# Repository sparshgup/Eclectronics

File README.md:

# Eclectronics
Olin College - Spring 2025 - Eclectronics

## [RP2350A Development Board](https://github.com/sparshgup/Eclectronics/tree/main/RP2350Adev)

## [MP1: USB-powered LED Flasher](https://github.com/sparshgup/Eclectronics/tree/main/MP1)

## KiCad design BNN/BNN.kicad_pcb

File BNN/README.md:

# Binary Neural Network Inference Accelerator PCB

Built a custom 2-layer PCB that combines an RP2040 microcontroller with a Lattice iCE40UP5K FPGA. The goal was to run a small binary neural network (BNN) classifier on the FPGA in hardware. The RP2040 programs the FPGA, sends input data over SPI, gets back a classification result, and prints it over USB serial. An RGB LED shows which class was picked.

BNNs use XNOR and popcount instead of floating-point math, which maps well onto FPGA lookup tables. The demo targets the Iris dataset (4 inputs, 3 classes). The hardware doesn't care what model you use since the weights are just baked into the FPGA bitstream.

The design is based on the open-source pico-ice board by tinyVision.ai and the riffpga framework by Psychogenic Technologies.

## Layout

## PCB

## Schematics

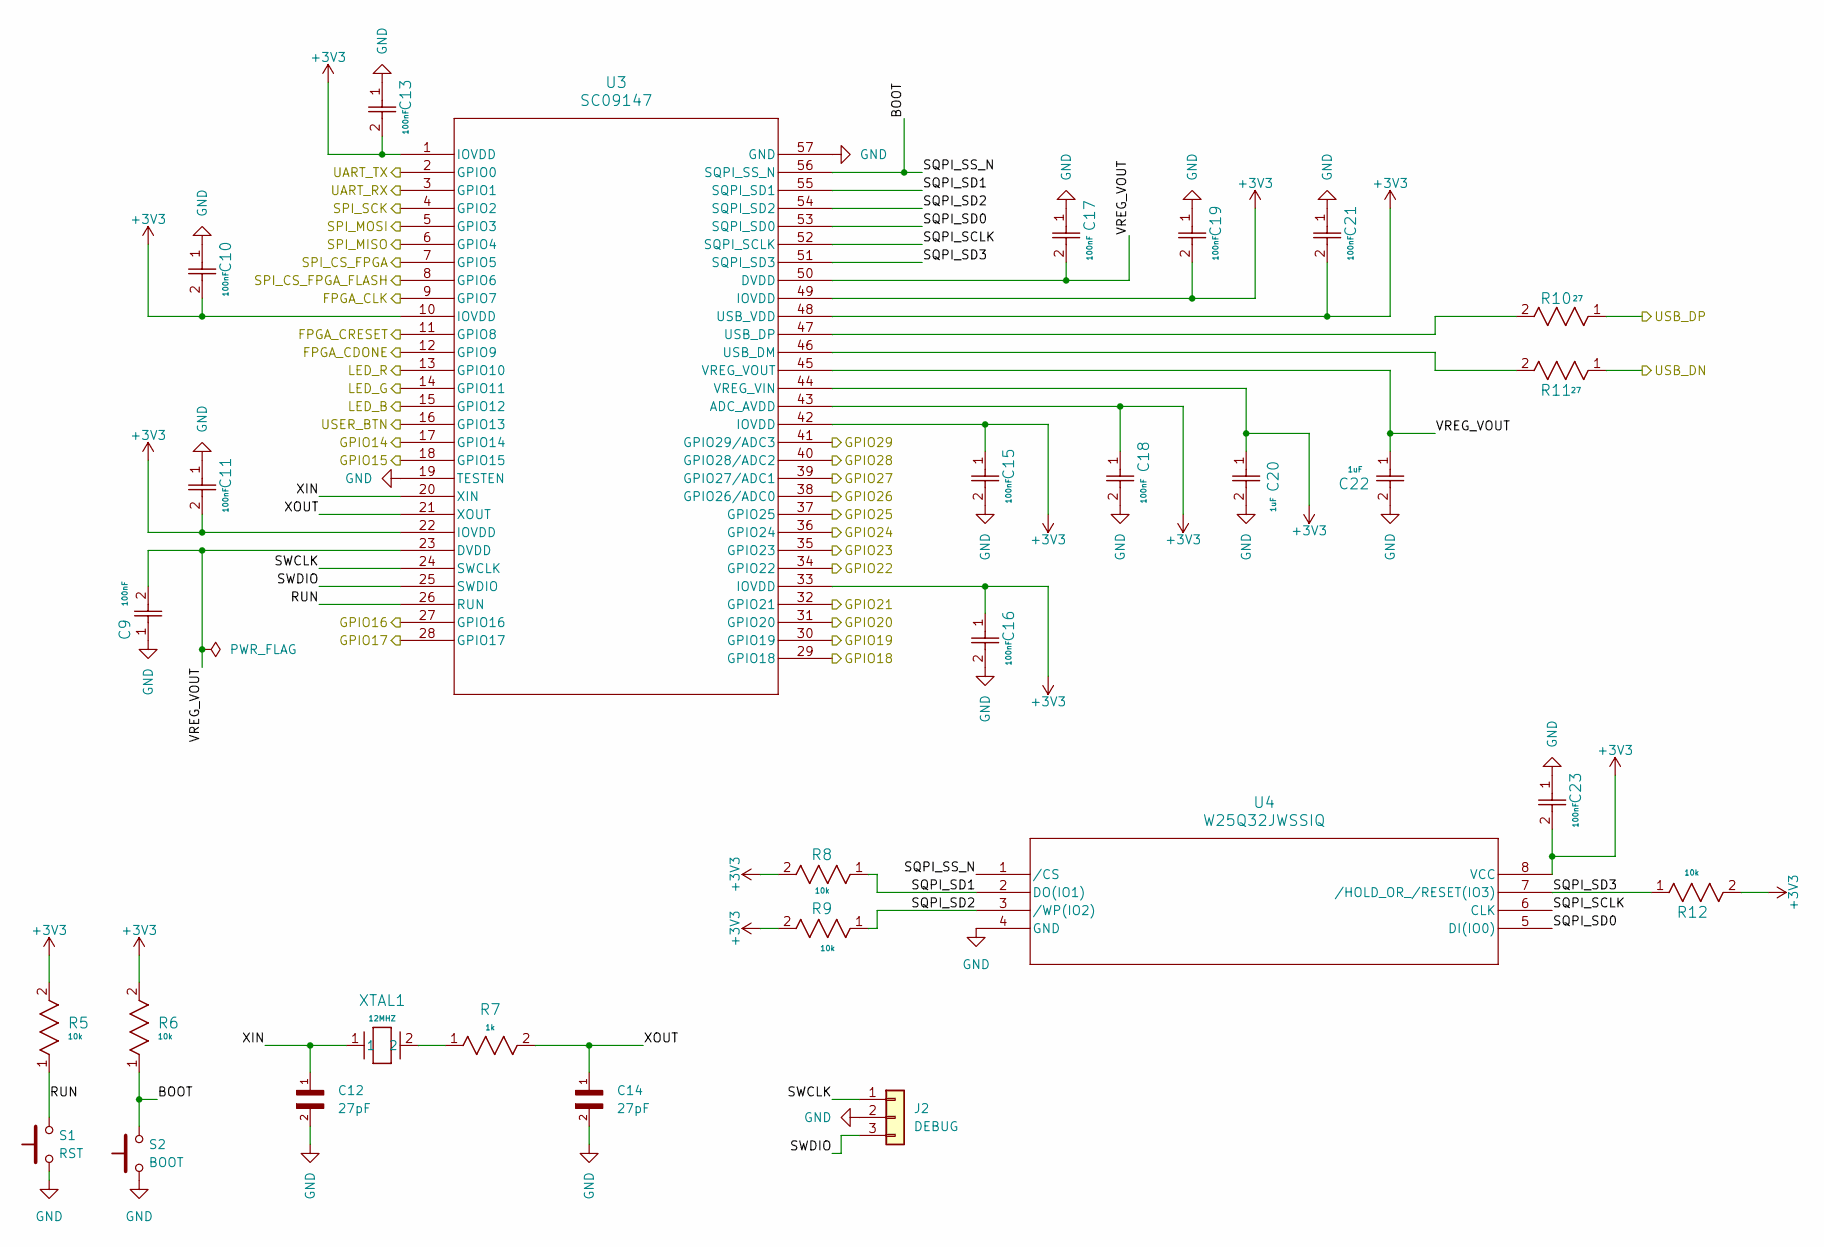
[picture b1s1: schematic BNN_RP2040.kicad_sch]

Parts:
C9, C10, C11, C13, C15, C16, C17, C18, C19, C21, C23: 100nF; CAP_CL10_SAM
C12, C14: 27pF; CAPC1608X90N; DigiKey_Part_Number 490-17767-1-ND
C20, C22: 1uF; CAP_GCM188_MUR
J2: DEBUG; PinHeader_1x03_P2.54mm_Vertical
R5, R6, R8, R9, R12: 10k; RC0603N_PAN
R7: 1k; RC0603N_YAG
R10, R11: 27; RC0603N_YAG
S1: RST; B3U-1000P
S2: BOOT; B3U-1000P
U3: SC09147; QFN56_7X7_RPI
U4: W25Q32JWSSIQ; SOIC-8_5P28X5P28_WIN
XTAL1: 12MHZ; XTAL_ABLS_ABR

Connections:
+3V3: C10.2, C11.2, C13.2, C15.1, C16.1, C18.1, C19.2, C20.1, C21.2, C23.2, R5.2, R6.2, R8.2, R9.2, R12.2, U3.1 (IOVDD), U3.10 (IOVDD), U3.22 (IOVDD), U3.33 (IOVDD), U3.42 (IOVDD), U3.43 (ADC_AVDD), U3.44 (VREG_VIN), U3.48 (USB_VDD), U3.49 (IOVDD), U4.8 (VCC); also elsewhere on the board
/IO/GPIO14: U3.17 (GPIO14); also elsewhere on the board
/IO/GPIO15: U3.18 (GPIO15); also elsewhere on the board
/IO/GPIO16: U3.27 (GPIO16); also elsewhere on the board
/IO/GPIO17: U3.28 (GPIO17); also elsewhere on the board
/IO/GPIO18: U3.29 (GPIO18); also elsewhere on the board
/IO/GPIO19: U3.30 (GPIO19); also elsewhere on the board
/IO/GPIO20: U3.31 (GPIO20); also elsewhere on the board
/IO/GPIO21: U3.32 (GPIO21); also elsewhere on the board
/IO/GPIO22: U3.34 (GPIO22); also elsewhere on the board
/IO/GPIO23: U3.35 (GPIO23); also elsewhere on the board
/IO/GPIO24: U3.36 (GPIO24); also elsewhere on the board
/IO/GPIO25: U3.37 (GPIO25); also elsewhere on the board
/IO/GPIO26: U3.38 (GPIO26/ADC0); also elsewhere on the board
/IO/GPIO27: U3.39 (GPIO27/ADC1); also elsewhere on the board
/IO/GPIO28: U3.40 (GPIO28/ADC2); also elsewhere on the board
/IO/GPIO29: U3.41 (GPIO29/ADC3); also elsewhere on the board
/IO/LED_B: U3.15 (GPIO12); also elsewhere on the board
/IO/LED_G: U3.14 (GPIO11); also elsewhere on the board
/IO/LED_R: U3.13 (GPIO10); also elsewhere on the board
/IO/USER_BTN: U3.16 (GPIO13); also elsewhere on the board
/Power/USB_DN: R11.1; also elsewhere on the board
/Power/USB_DP: R10.1; also elsewhere on the board
/RP2040/BOOT: R6.1, S2.2, U3.56 (SQPI_SS_N), U4.1 (/CS)
/RP2040/FPGA_CDONE: U3.12 (GPIO9); also elsewhere on the board
/RP2040/FPGA_CLK: U3.9 (GPIO7); also elsewhere on the board
/RP2040/FPGA_CRESET: U3.11 (GPIO8); also elsewhere on the board
/RP2040/RUN: R5.1, S1.2, U3.26 (RUN)
/RP2040/SPI_CS_FPGA: U3.7 (GPIO5); also elsewhere on the board
/RP2040/SQPI_SCLK: U3.52 (SQPI_SCLK), U4.6 (CLK)
/RP2040/SQPI_SD0: U3.53 (SQPI_SD0), U4.5 (DI(IO0))
/RP2040/SQPI_SD1: R8.1, U3.55 (SQPI_SD1), U4.2 (DO(IO1))
/RP2040/SQPI_SD2: R9.1, U3.54 (SQPI_SD2), U4.3 (/WP(IO2))
/RP2040/SQPI_SD3: R12.1, U3.51 (SQPI_SD3), U4.7 (/HOLD_OR_/RESET(IO3))
/RP2040/SWCLK: J2.1, U3.24 (SWCLK)
/RP2040/SWDIO: J2.3, U3.25 (SWDIO)
/RP2040/UART_RX: U3.3 (GPIO1); also elsewhere on the board
/RP2040/UART_TX: U3.2 (GPIO0); also elsewhere on the board
/RP2040/VREG_VOUT: C9.2, C17.2, C22.1, U3.23 (DVDD), U3.45 (VREG_VOUT), U3.50 (DVDD)
/RP2040/XIN: C12.1, U3.20 (XIN), XTAL1.1
/RP2040/XOUT: C14.1, R7.2, U3.21 (XOUT)
/iCE40UP5K/SPI_S0: U3.6 (GPIO4); also elsewhere on the board
/iCE40UP5K/SPI_SCK: U3.4 (GPIO2); also elsewhere on the board
/iCE40UP5K/SPI_SI: U3.5 (GPIO3); also elsewhere on the board
/iCE40UP5K/SPI_SS: U3.8 (GPIO6); also elsewhere on the board
GND: C9.1, C10.1, C11.1, C12.2, C13.1, C14.2, C15.2, C16.2, C17.1, C18.2, C19.1, C20.2, C21.1, C22.2, C23.1, J2.2, S1.1, S2.1, U3.19 (TESTEN), U3.57 (GND), U4.4 (GND); also elsewhere on the board
unnamed: R7.1, XTAL1.2
unnamed: R11.2, U3.46 (USB_DM)
unnamed: R10.2, U3.47 (USB_DP)

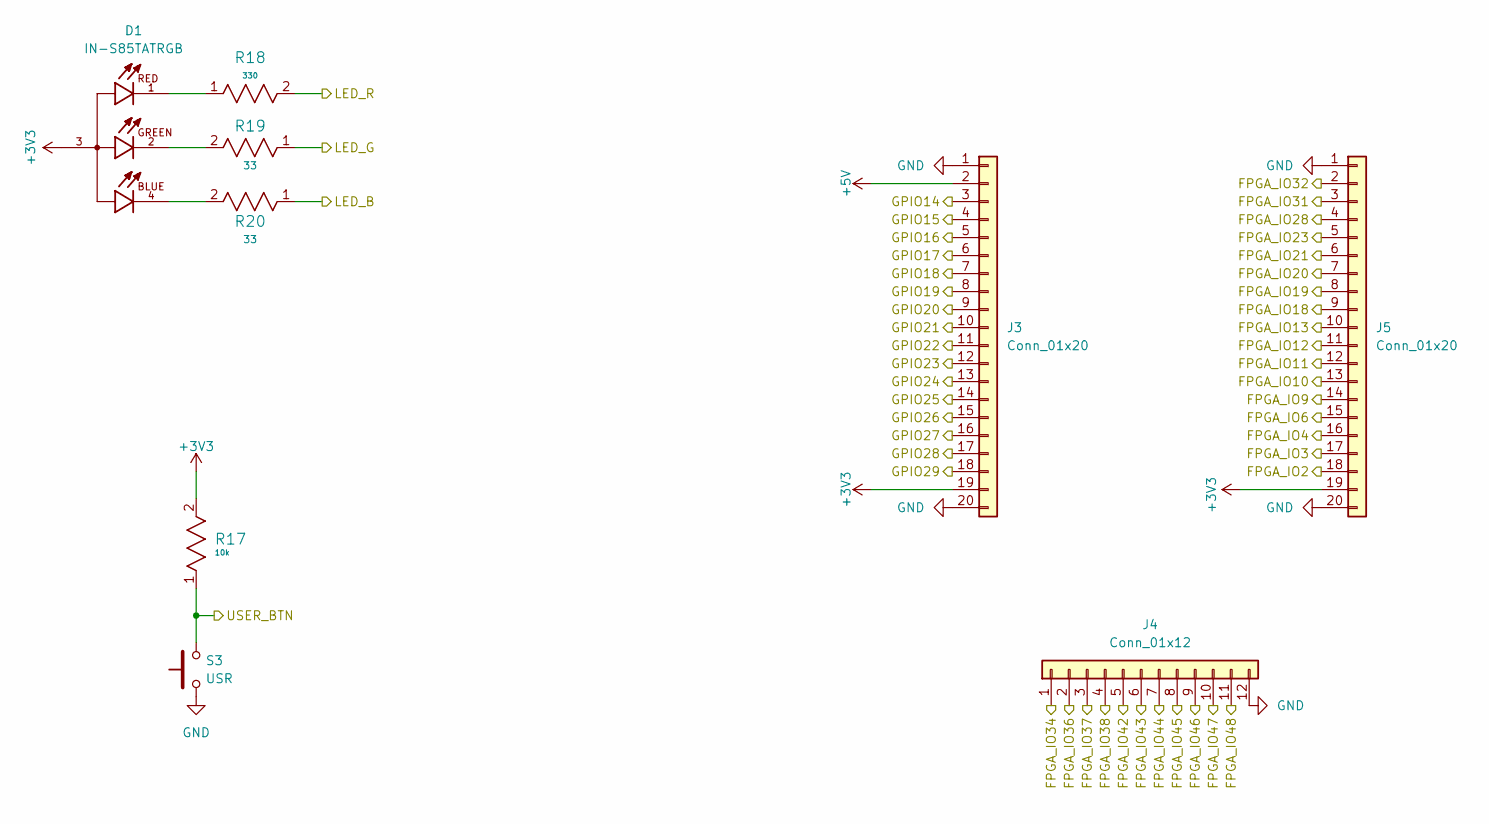
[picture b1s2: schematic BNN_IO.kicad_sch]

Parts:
D1: IN-S85TATRGB; LEDSC70P200X125X110-4N; PARTREV 1.0; DigiKey_Part_Number 1830-1086-1-ND
J3, J5: Conn_01x20; PinHeader_1x20_P2.54mm_Vertical
J4: Conn_01x12; PinHeader_1x12_P2.54mm_Vertical
R17: 10k; RC0603N_PAN
R18: 330; RC0603N_YAG
R19, R20: 33; RC0603N_YAG
S3: USR; B3U-1000P

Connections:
+3V3: D1.3, J3.19, J5.19, R17.2; also elsewhere on the board
+5V: J3.2; also elsewhere on the board
/IO/FPGA_IO2: J5.18; also elsewhere on the board
/IO/FPGA_IO3: J5.17; also elsewhere on the board
/IO/FPGA_IO4: J5.16; also elsewhere on the board
/IO/FPGA_IO6: J5.15; also elsewhere on the board
/IO/FPGA_IO9: J5.14; also elsewhere on the board
/IO/FPGA_IO10: J5.13; also elsewhere on the board
/IO/FPGA_IO11: J5.12; also elsewhere on the board
/IO/FPGA_IO12: J5.11; also elsewhere on the board
/IO/FPGA_IO13: J5.10; also elsewhere on the board
/IO/FPGA_IO18: J5.9; also elsewhere on the board
/IO/FPGA_IO19: J5.8; also elsewhere on the board
/IO/FPGA_IO20: J5.7; also elsewhere on the board
/IO/FPGA_IO21: J5.6; also elsewhere on the board
/IO/FPGA_IO23: J5.5; also elsewhere on the board
/IO/FPGA_IO28: J5.4; also elsewhere on the board
/IO/FPGA_IO31: J5.3; also elsewhere on the board
/IO/FPGA_IO32: J5.2; also elsewhere on the board
/IO/FPGA_IO34: J4.1; also elsewhere on the board
/IO/FPGA_IO36: J4.2; also elsewhere on the board
/IO/FPGA_IO37: J4.3; also elsewhere on the board
/IO/FPGA_IO38: J4.4; also elsewhere on the board
/IO/FPGA_IO42: J4.5; also elsewhere on the board
/IO/FPGA_IO43: J4.6; also elsewhere on the board
/IO/FPGA_IO44: J4.7; also elsewhere on the board
/IO/FPGA_IO45: J4.8; also elsewhere on the board
/IO/FPGA_IO46: J4.9; also elsewhere on the board
/IO/FPGA_IO47: J4.10; also elsewhere on the board
/IO/FPGA_IO48: J4.11; also elsewhere on the board
/IO/GPIO14: J3.3; also elsewhere on the board
/IO/GPIO15: J3.4; also elsewhere on the board
/IO/GPIO16: J3.5; also elsewhere on the board
/IO/GPIO17: J3.6; also elsewhere on the board
/IO/GPIO18: J3.7; also elsewhere on the board
/IO/GPIO19: J3.8; also elsewhere on the board
/IO/GPIO20: J3.9; also elsewhere on the board
/IO/GPIO21: J3.10; also elsewhere on the board
/IO/GPIO22: J3.11; also elsewhere on the board
/IO/GPIO23: J3.12; also elsewhere on the board
/IO/GPIO24: J3.13; also elsewhere on the board
/IO/GPIO25: J3.14; also elsewhere on the board
/IO/GPIO26: J3.15; also elsewhere on the board
/IO/GPIO27: J3.16; also elsewhere on the board
/IO/GPIO28: J3.17; also elsewhere on the board
/IO/GPIO29: J3.18; also elsewhere on the board
/IO/LED_B: R20.1; also elsewhere on the board
/IO/LED_G: R19.1; also elsewhere on the board
/IO/LED_R: R18.2; also elsewhere on the board
/IO/USER_BTN: R17.1, S3.2; also elsewhere on the board
GND: J3.1, J3.20, J4.12, J5.1, J5.20, S3.1; also elsewhere on the board
unnamed: D1.1, R18.1
unnamed: D1.2, R19.2
unnamed: D1.4, R20.2

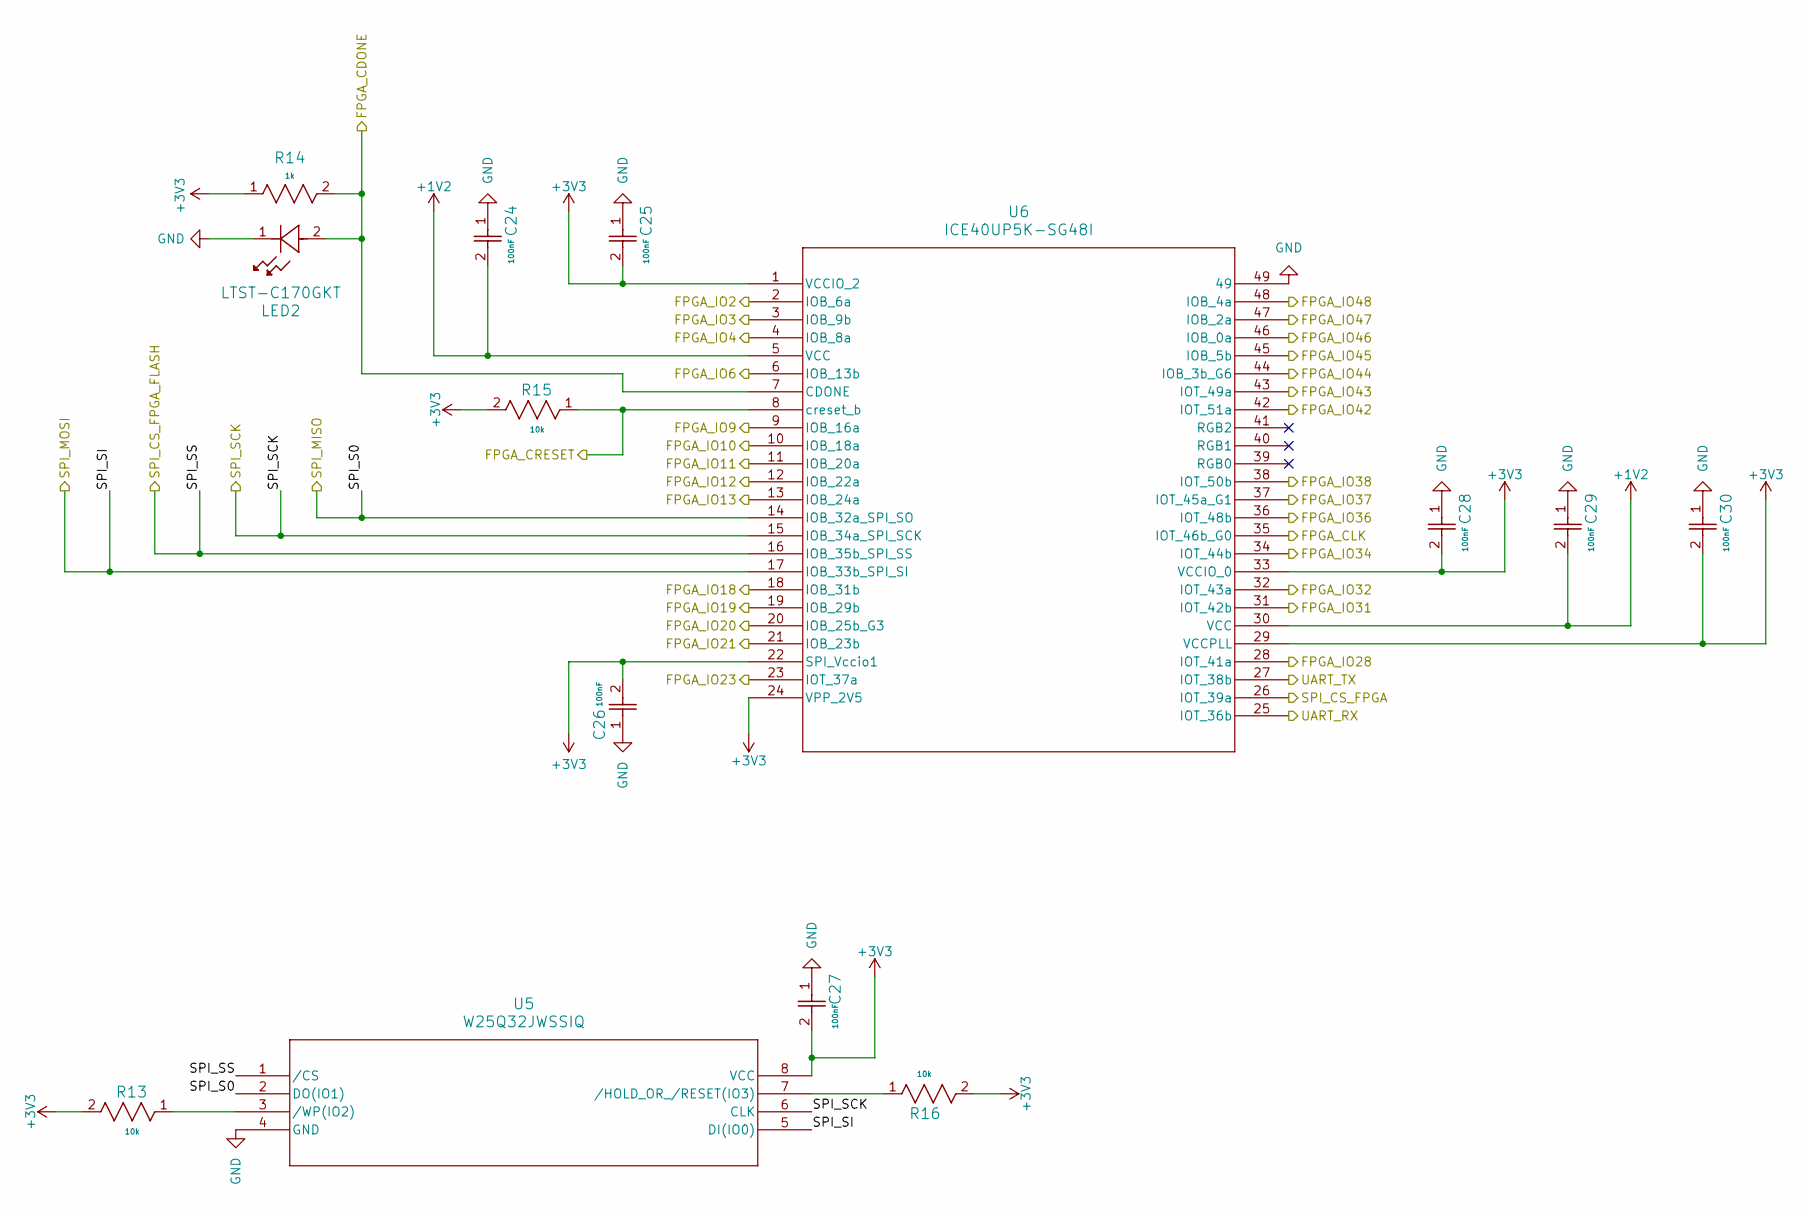
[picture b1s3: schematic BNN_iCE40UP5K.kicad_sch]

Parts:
C24, C25, C26, C27, C28, C29, C30: 100nF; CAP_CL10_SAM
LED2: LTST-C170GKT; LED_LTST-C170GKT_LTO
R13, R15, R16: 10k; RC0603N_PAN
R14: 1k; RC0603N_YAG
U5: W25Q32JWSSIQ; SOIC-8_5P28X5P28_WIN
U6: ICE40UP5K-SG48I; QFN-48-1EP_7x7mm_P0.5mm_EP5.6x5.6mm

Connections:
+1V2: C24.2, C29.2, U6.5 (VCC), U6.30 (VCC); also elsewhere on the board
+3V3: C25.2, C26.2, C27.2, C28.2, C30.2, R13.2, R14.1, R15.2, R16.2, U5.8 (VCC), U6.1 (VCCIO_2), U6.22 (SPI_Vccio1), U6.24 (VPP_2V5), U6.29 (VCCPLL), U6.33 (VCCIO_0); also elsewhere on the board
/IO/FPGA_IO2: U6.2 (IOB_6a); also elsewhere on the board
/IO/FPGA_IO3: U6.3 (IOB_9b); also elsewhere on the board
/IO/FPGA_IO4: U6.4 (IOB_8a); also elsewhere on the board
/IO/FPGA_IO6: U6.6 (IOB_13b); also elsewhere on the board
/IO/FPGA_IO9: U6.9 (IOB_16a); also elsewhere on the board
/IO/FPGA_IO10: U6.10 (IOB_18a); also elsewhere on the board
/IO/FPGA_IO11: U6.11 (IOB_20a); also elsewhere on the board
/IO/FPGA_IO12: U6.12 (IOB_22a); also elsewhere on the board
/IO/FPGA_IO13: U6.13 (IOB_24a); also elsewhere on the board
/IO/FPGA_IO18: U6.18 (IOB_31b); also elsewhere on the board
/IO/FPGA_IO19: U6.19 (IOB_29b); also elsewhere on the board
/IO/FPGA_IO20: U6.20 (IOB_25b_G3); also elsewhere on the board
/IO/FPGA_IO21: U6.21 (IOB_23b); also elsewhere on the board
/IO/FPGA_IO23: U6.23 (IOT_37a); also elsewhere on the board
/IO/FPGA_IO28: U6.28 (IOT_41a); also elsewhere on the board
/IO/FPGA_IO31: U6.31 (IOT_42b); also elsewhere on the board
/IO/FPGA_IO32: U6.32 (IOT_43a); also elsewhere on the board
/IO/FPGA_IO34: U6.34 (IOT_44b); also elsewhere on the board
/IO/FPGA_IO36: U6.36 (IOT_48b); also elsewhere on the board
/IO/FPGA_IO37: U6.37 (IOT_45a_G1); also elsewhere on the board
/IO/FPGA_IO38: U6.38 (IOT_50b); also elsewhere on the board
/IO/FPGA_IO42: U6.42 (IOT_51a); also elsewhere on the board
/IO/FPGA_IO43: U6.43 (IOT_49a); also elsewhere on the board
/IO/FPGA_IO44: U6.44 (IOB_3b_G6); also elsewhere on the board
/IO/FPGA_IO45: U6.45 (IOB_5b); also elsewhere on the board
/IO/FPGA_IO46: U6.46 (IOB_0a); also elsewhere on the board
/IO/FPGA_IO47: U6.47 (IOB_2a); also elsewhere on the board
/IO/FPGA_IO48: U6.48 (IOB_4a); also elsewhere on the board
/RP2040/FPGA_CDONE: LED2.2, R14.2, U6.7 (CDONE); also elsewhere on the board
/RP2040/FPGA_CLK: U6.35 (IOT_46b_G0); also elsewhere on the board
/RP2040/FPGA_CRESET: R15.1, U6.8 (creset_b); also elsewhere on the board
/RP2040/SPI_CS_FPGA: U6.26 (IOT_39a); also elsewhere on the board
/RP2040/UART_RX: U6.25 (IOT_36b); also elsewhere on the board
/RP2040/UART_TX: U6.27 (IOT_38b); also elsewhere on the board
/iCE40UP5K/SPI_S0: U5.2 (DO(IO1)), U6.14 (IOB_32a_SPI_SO); also elsewhere on the board
/iCE40UP5K/SPI_SCK: U5.6 (CLK), U6.15 (IOB_34a_SPI_SCK); also elsewhere on the board
/iCE40UP5K/SPI_SI: U5.5 (DI(IO0)), U6.17 (IOB_33b_SPI_SI); also elsewhere on the board
/iCE40UP5K/SPI_SS: U5.1 (/CS), U6.16 (IOB_35b_SPI_SS); also elsewhere on the board
GND: C24.1, C25.1, C26.1, C27.1, C28.1, C29.1, C30.1, LED2.1, U5.4 (GND), U6.49; also elsewhere on the board
unnamed: R16.1, U5.7 (/HOLD_OR_/RESET(IO3))
unnamed: R13.1, U5.3 (/WP(IO2))

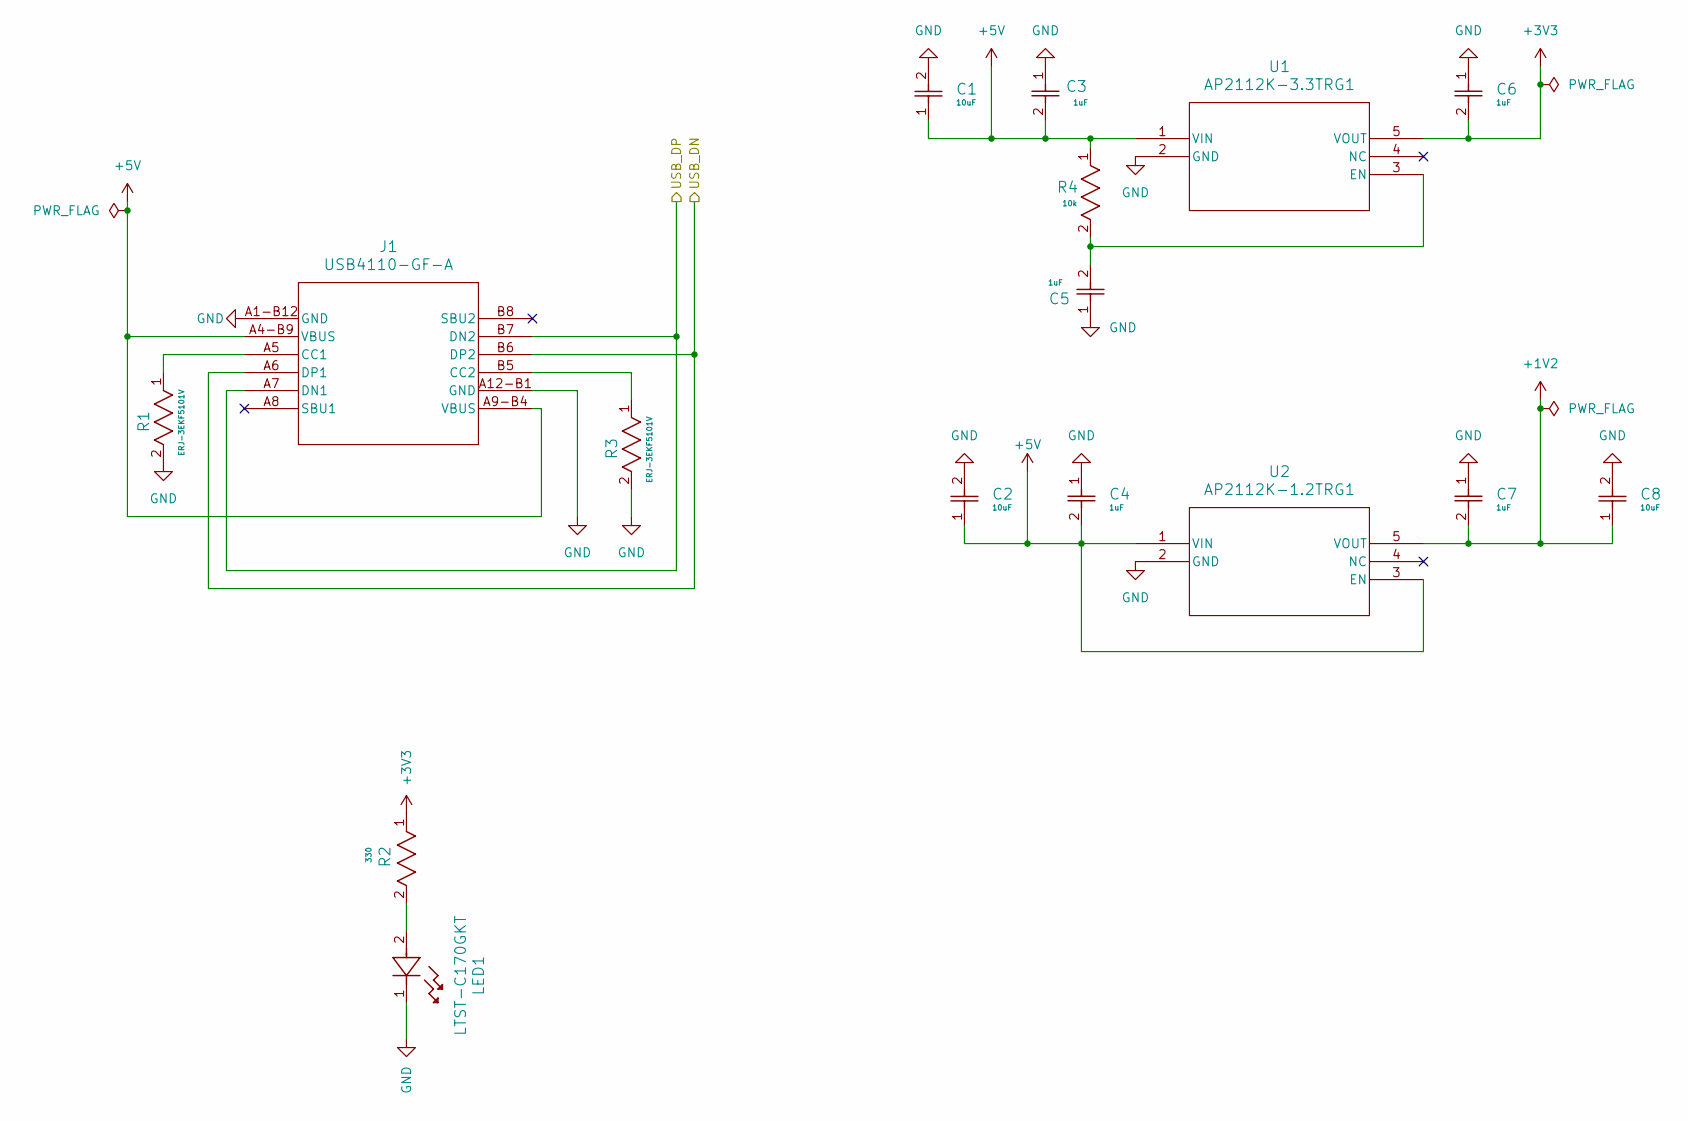
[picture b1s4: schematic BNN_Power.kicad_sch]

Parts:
C1, C2, C8: 10uF; CAP_GRM188_&plus_&slash_-0.2_MUR
C3, C4, C5, C6, C7: 1uF; CAP_GCM188_MUR
J1: USB4110-GF-A; USB4110-GF-A_GCT
LED1: LTST-C170GKT; LED_LTST-C170GKT_LTO
R1, R3: ERJ-3EKF5101V; RC0603N_PAN
R2: 330; RC0603N_YAG
R4: 10k; RC0603N_PAN
U1: AP2112K-3.3TRG1; SOT_RG1_DIO
U2: AP2112K-1.2TRG1; SOT_RG1_DIO

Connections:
+1V2: C7.2, C8.1, U2.5 (VOUT); also elsewhere on the board
+3V3: C6.2, R2.1, U1.5 (VOUT); also elsewhere on the board
+5V: C1.1, C2.1, C3.2, C4.2, J1.A4-B9 (VBUS), J1.A9-B4 (VBUS), R4.1, U1.1 (VIN), U2.1 (VIN), U2.3 (EN); also elsewhere on the board
/Power/USB_DN: J1.A6 (DP1), J1.B6 (DP2); also elsewhere on the board
/Power/USB_DP: J1.A7 (DN1), J1.B7 (DN2); also elsewhere on the board
GND: C1.2, C2.2, C3.1, C4.1, C5.1, C6.1, C7.1, C8.2, J1.A1-B12 (GND), J1.A12-B1 (GND), LED1.1, R1.2, R3.2, U1.2 (GND), U2.2 (GND); also elsewhere on the board
unnamed: J1.A5 (CC1), R1.1
unnamed: J1.B5 (CC2), R3.1
unnamed: LED1.2, R2.2
unnamed: C5.2, R4.2, U1.3 (EN)

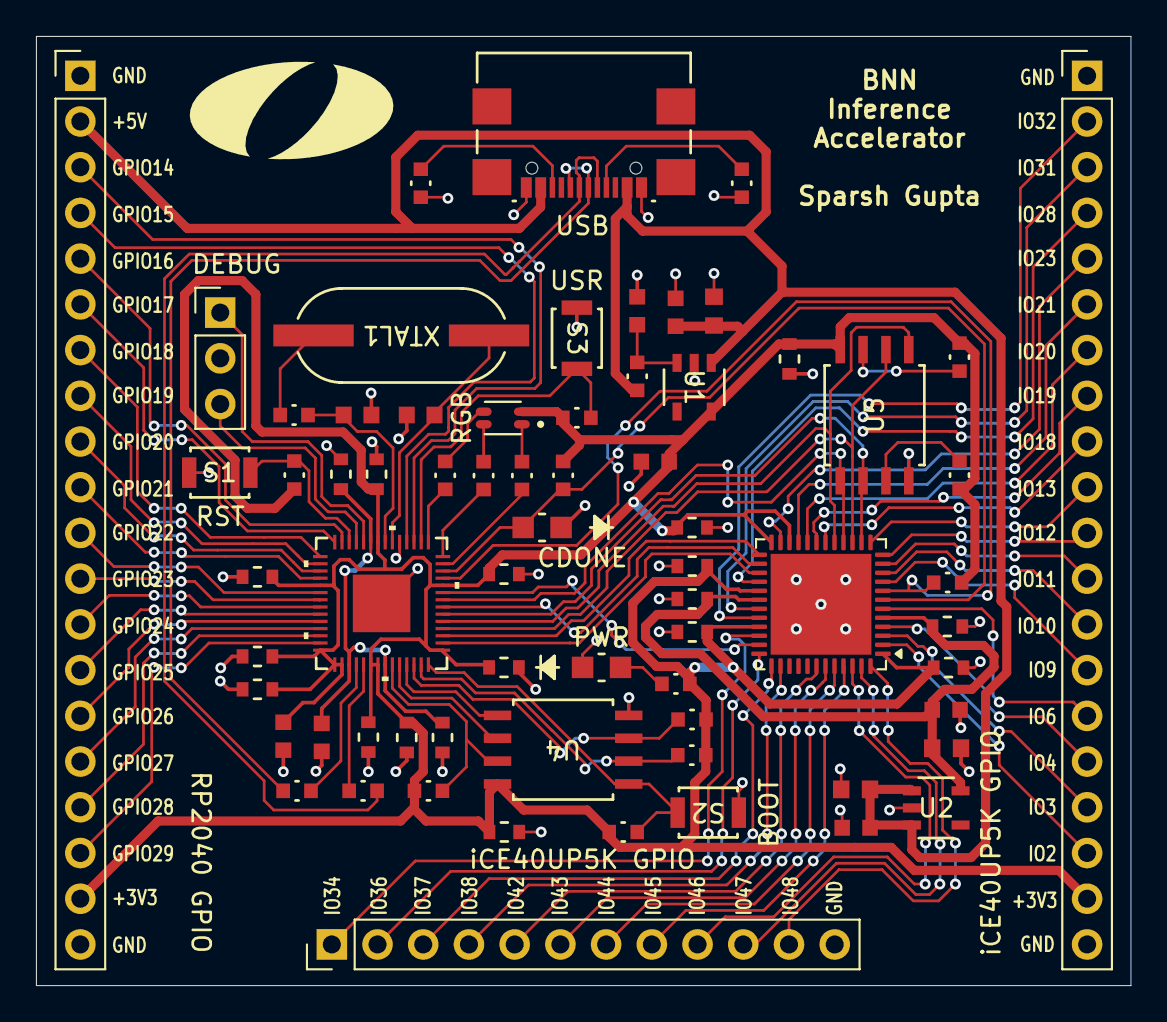
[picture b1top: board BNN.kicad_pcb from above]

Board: 2 copper layers, 60.8 x 52.7 mm, 69 parts (0 on the bottom side), 88 nets.

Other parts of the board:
OlinLogoLg: G***; OlinLogoLg

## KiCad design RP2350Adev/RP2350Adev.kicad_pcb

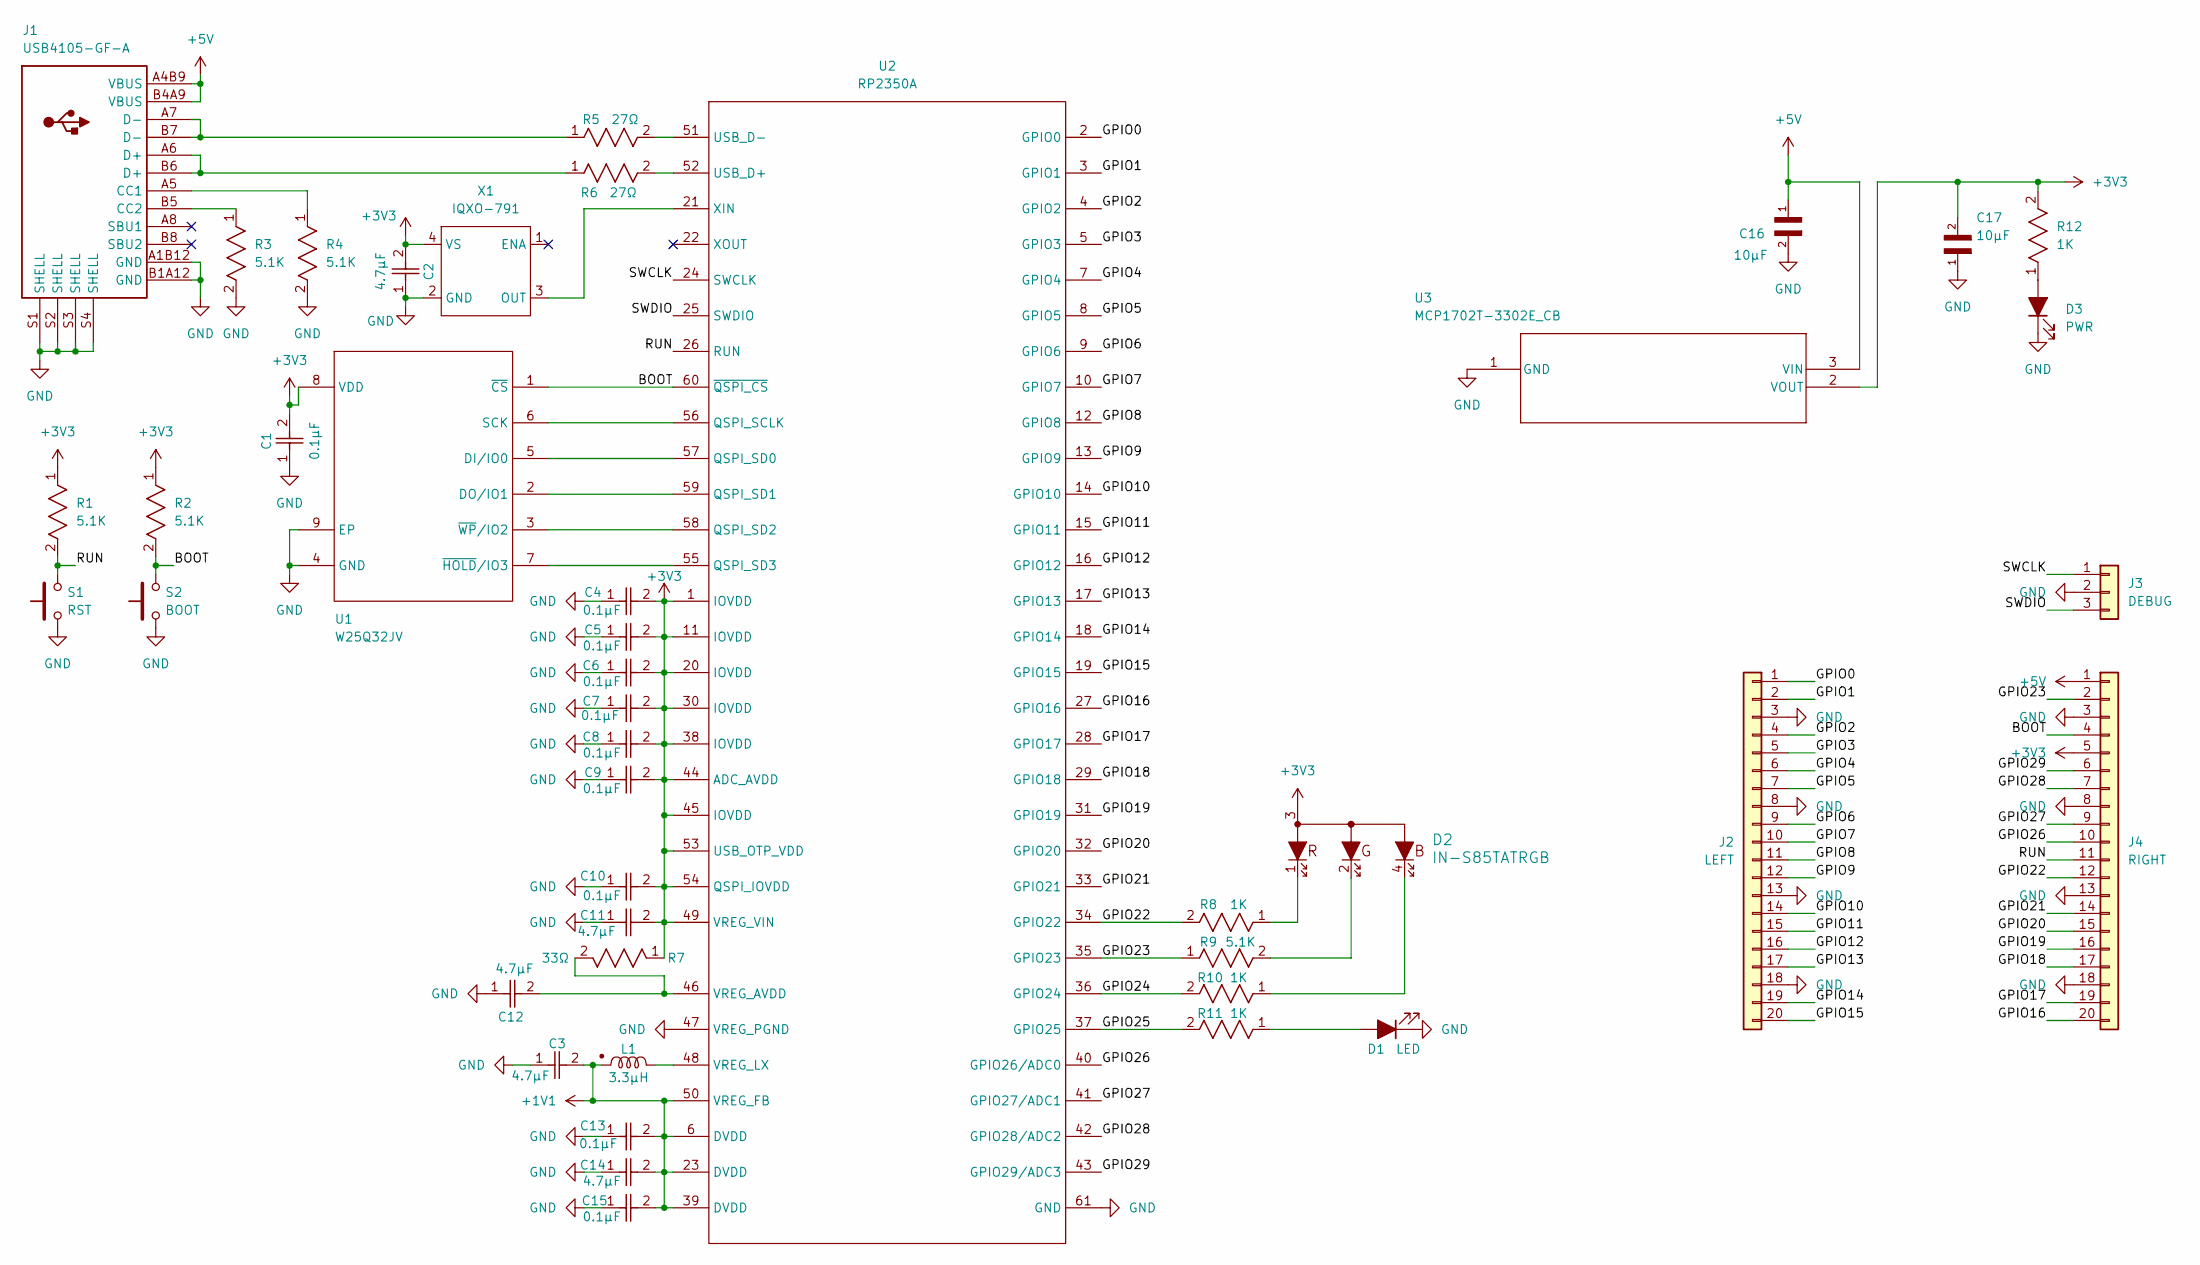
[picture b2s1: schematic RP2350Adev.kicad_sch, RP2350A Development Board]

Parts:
C1, C4, C5, C6, C7, C8, C9, C10, C13, C15: 0.1µF; CAP_CL10_SAM
C2, C3, C11, C12, C14: 4.7µF; CAP_GRM188D_MUR
C16, C17: 10µF; CAPC1608X100N; DigiKey_Part_Number 490-18214-1-ND
D1: LED; LED_0805_2012Metric
D2: IN-S85TATRGB
D3: PWR; LED_0805_2012Metric
J1: USB4105-GF-A
J2: LEFT; PinHeader_1x20_P2.54mm_Vertical
J3: DEBUG; PinHeader_1x03_P2.54mm_Vertical
J4: RIGHT; PinHeader_1x20_P2.54mm_Vertical
L1: 3.3µH; AOTA-B201610S3R3-101-T
R1, R2, R3, R4, R9: 5.1K; RC0603N_PAN
R5, R6: 27Ω; RC0603N_YAG
R7: 33Ω; RC0603N_YAG
R8, R10, R11, R12: 1K; RC0603N_YAG
S1: RST; B3U-1000P
S2: BOOT; B3U-1000P
U1: W25Q32JV; WSON-8-1EP_6x5mm_P1.27mm_EP3.4x4.3mm
U2: RP2350A; RP2350A_QFN-60_EP_7.75x7.75_Pitch0.4mm
U3: MCP1702T-3302E_CB; SOT-23A_MC_MCH
X1: IQXO-791

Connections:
+1V1: C3.2, C13.2, C14.2, C15.2, L1.1, U2.6 (DVDD), U2.23 (DVDD), U2.39 (DVDD), U2.50 (VREG_FB)
+3V3: C1.2, C2.2, C4.2, C5.2, C6.2, C7.2, C8.2, C9.2, C10.2, C11.2, C17.2, D2.3, J4.5, R1.1, R2.1, R7.1, R12.2, U1.8 (VDD), U2.1 (IOVDD), U2.11 (IOVDD), U2.20 (IOVDD), U2.30 (IOVDD), U2.38 (IOVDD), U2.44 (ADC_AVDD), U2.45 (IOVDD), U2.49 (VREG_VIN), U2.53 (USB_OTP_VDD), U2.54 (QSPI_IOVDD), U3.2 (VOUT), X1.4 (VS)
+5V: C16.1, J1.A4B9 (VBUS), J1.B4A9 (VBUS), J4.1, U3.3 (VIN)
/BOOT: J4.4, R2.2, S2.2, U1.1 (~CS), U2.60 (~QSPI_CS)
/GPIO0: J2.1, U2.2 (GPIO0)
/GPIO1: J2.2, U2.3 (GPIO1)
/GPIO2: J2.4, U2.4 (GPIO2)
/GPIO3: J2.5, U2.5 (GPIO3)
/GPIO4: J2.6, U2.7 (GPIO4)
/GPIO5: J2.7, U2.8 (GPIO5)
/GPIO6: J2.9, U2.9 (GPIO6)
/GPIO7: J2.10, U2.10 (GPIO7)
/GPIO8: J2.11, U2.12 (GPIO8)
/GPIO9: J2.12, U2.13 (GPIO9)
/GPIO10: J2.14, U2.14 (GPIO10)
/GPIO11: J2.15, U2.15 (GPIO11)
/GPIO12: J2.16, U2.16 (GPIO12)
/GPIO13: J2.17, U2.17 (GPIO13)
/GPIO14: J2.19, U2.18 (GPIO14)
/GPIO15: J2.20, U2.19 (GPIO15)
/GPIO16: J4.20, U2.27 (GPIO16)
/GPIO17: J4.19, U2.28 (GPIO17)
/GPIO18: J4.17, U2.29 (GPIO18)
/GPIO19: J4.16, U2.31 (GPIO19)
/GPIO20: J4.15, U2.32 (GPIO20)
/GPIO21: J4.14, U2.33 (GPIO21)
/GPIO22: J4.12, R8.2, U2.34 (GPIO22)
/GPIO23: J4.2, R9.1, U2.35 (GPIO23)
/GPIO24: R10.2, U2.36 (GPIO24)
/GPIO25: R11.2, U2.37 (GPIO25)
/GPIO26: J4.10, U2.40 (GPIO26/ADC0)
/GPIO27: J4.9, U2.41 (GPIO27/ADC1)
/GPIO28: J4.7, U2.42 (GPIO28/ADC2)
/GPIO29: J4.6, U2.43 (GPIO29/ADC3)
/RUN: J4.11, R1.2, S1.2, U2.26 (RUN)
/SWCLK: J3.1, U2.24 (SWCLK)
/SWDIO: J3.3, U2.25 (SWDIO)
GND: C1.1, C2.1, C3.1, C4.1, C5.1, C6.1, C7.1, C8.1, C9.1, C10.1, C11.1, C12.1, C13.1, C14.1, C15.1, C16.2, C17.1, D1.1 (K), D3.1 (K), J1.A1B12 (GND), J1.B1A12 (GND), J1.S1 (SHELL), J1.S2 (SHELL), J1.S3 (SHELL), J1.S4 (SHELL), J2.3, J2.8, J2.13, J2.18, J3.2, J4.3, J4.8, J4.13, J4.18, R3.2, R4.2, S1.1, S2.1, U1.4 (GND), U1.9 (EP), U2.47 (VREG_PGND), U2.61 (GND), U3.1 (GND), X1.2 (GND)
unnamed: D1.2 (A), R11.1
unnamed: D2.1, R8.1
unnamed: D2.2, R9.2
unnamed: D2.4, R10.1
unnamed: D3.2 (A), R12.1
unnamed: J1.A5 (CC1), R4.1
unnamed: J1.B5 (CC2), R3.1
unnamed: J1.A6 (D+), J1.B6 (D+), R6.1
unnamed: J1.A7 (D-), J1.B7 (D-), R5.1
unnamed: U1.5 (DI/IO0), U2.57 (QSPI_SD0)
unnamed: U1.2 (DO/IO1), U2.59 (QSPI_SD1)
unnamed: U1.6 (SCK), U2.56 (QSPI_SCLK)
unnamed: U1.7 (~HOLD/IO3), U2.55 (QSPI_SD3)
unnamed: U1.3 (~WP/IO2), U2.58 (QSPI_SD2)
unnamed: R6.2, U2.52 (USB_D+)
unnamed: R5.2, U2.51 (USB_D-)
unnamed: C12.2, R7.2, U2.46 (VREG_AVDD)
unnamed: L1.2, U2.48 (VREG_LX)
unnamed: U2.21 (XIN), X1.3 (OUT)

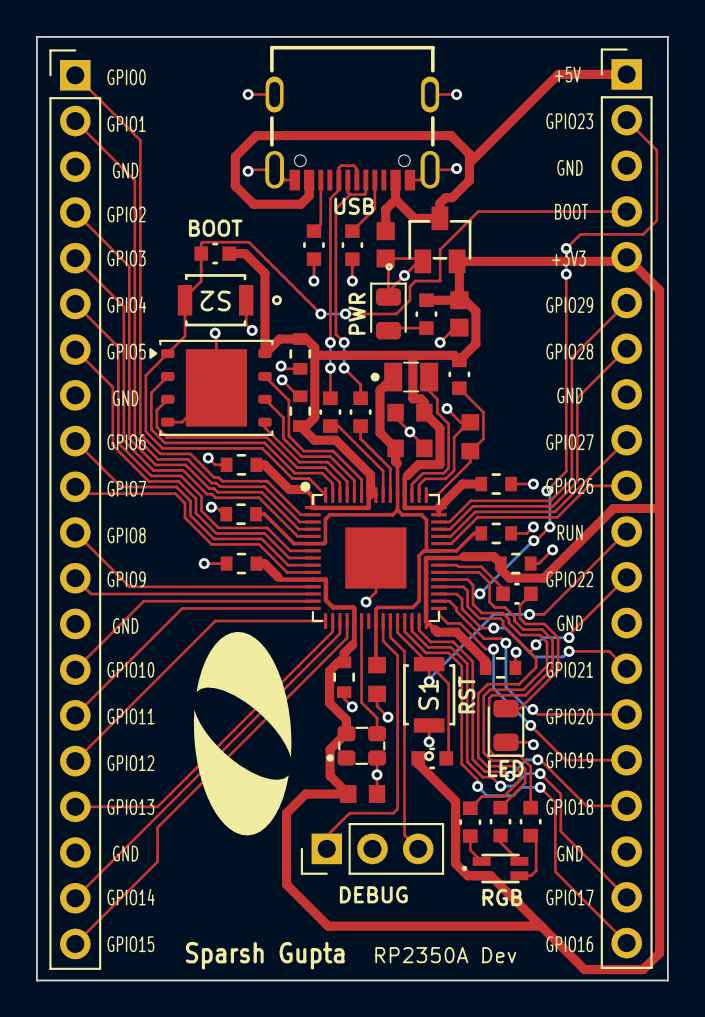
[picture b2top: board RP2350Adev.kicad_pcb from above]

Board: 2 copper layers, 35.1 x 52.4 mm, 44 parts (0 on the bottom side), 57 nets.

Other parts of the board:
OlinLogoLg: G***; OlinLogoLg
